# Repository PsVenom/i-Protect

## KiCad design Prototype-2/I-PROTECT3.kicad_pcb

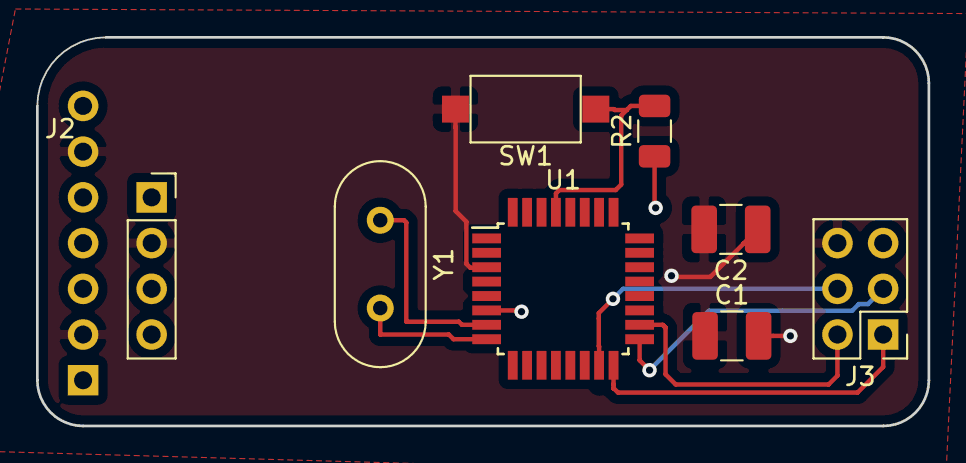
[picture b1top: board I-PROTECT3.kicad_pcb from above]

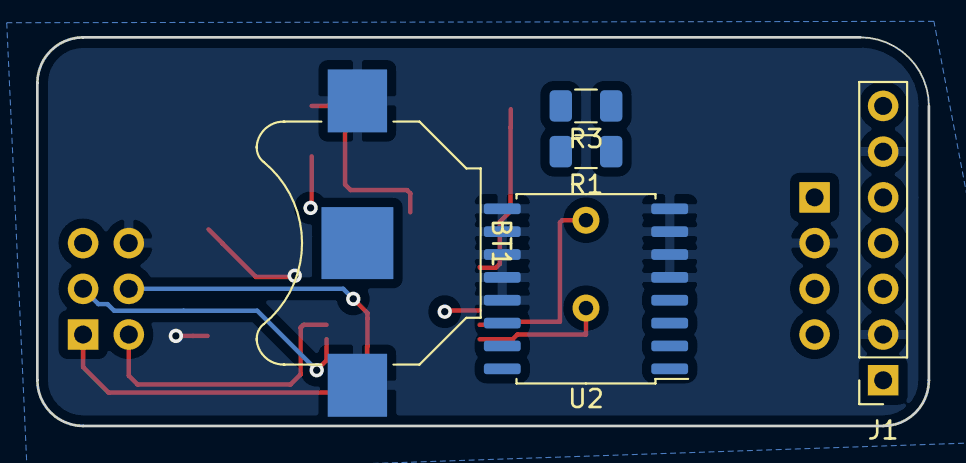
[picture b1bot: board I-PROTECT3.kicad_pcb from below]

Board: 4 copper layers, 49.5 x 21.6 mm, 13 parts (5 on the bottom side), 14 nets.

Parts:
BT1: CR1220; BatteryHolder_Keystone_3000_1x12mm
C1, C2: C_Small; C_1210_3225Metric_Pad1.42x2.65mm_HandSolder
J1: SIM 800; PinSocket_1x07_P2.54mm_Vertical
J2: SSD1306; PinSocket_1x04_P2.54mm_Vertical
J3: AVR ISP; PinHeader_2x03_P2.54mm_Vertical
R1, R3: R; R_1206_3216Metric
R2: R_Small; R_1206_3216Metric
SW1: SW_Push_Open; SW_SPST_CK_RS282G05A3
U1: ATmega328P-AU; TQFP-32_7x7mm_P0.8mm
U2: DS3231M; SOIC-16W_7.5x10.3mm_P1.27mm
Y1: Crystal; Crystal_HC49-4H_Vertical

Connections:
D11: J3.4, U1.15
D12: J3.1, U1.16
D13: J3.3, U1.17
GND: BT1.1, C1.1, C2.2, J1.2, J1.6, J2.2, J3.6, SW1.2, U1.3, U1.5, U1.21, U2.5, U2.6, U2.7, U2.8, U2.9, U2.10, U2.11, U2.12, U2.13
unnamed: BT1.2, U2.14
unnamed: C2.1, U1.8, Y1.2
unnamed: R1.1, R3.1
unnamed: U1.7, Y1.1
RST: J3.5, R2.2, SW1.1, U1.29
RX: J1.5, U1.30
SCL: J2.3, R3.2, U1.28, U2.16
SDA: J2.4, R1.2, U1.27, U2.15
TX: J1.4, U1.31
VCC: J1.1, J1.3, J3.2, R2.1, U1.4, U1.6, U1.18, U2.2
